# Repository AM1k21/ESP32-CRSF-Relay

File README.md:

# ESP32-CRSF-Relay

A high-performance **CRSF Relay Node** that extends the range of your radio link by forwarding CRSF packets from an ELRS Receiver to a high-power TX Module.

## 🚀 Key Capabilities

* **CRSF frames forwarding** Forwards frames from receiver to transmitter to further range of radio link
* **Dual-Core Architecture:** Radio logic runs exclusively on **Core 1** (High Priority) to ensure 0% packet loss, while WiFi runs on **Core 0**.
* **WiFi Manager:** Integrated web dashboard at `192.168.4.1` (No app required).
* **Live Telemetry:** Real-time scrolling graph of RSSI and Link Quality to visualize signal health and live channel values streaming.
* **Safety Limiter:** Adjustable throttle scaling (0-100%) via the web interface—perfect for training beginners without reprogramming the radio.
* **Smart Status:** Instantly diagnoses connection issues (e.g., "RC LOST", "MODULE OFF", "DRONE LOST").

## 🛠️ Hardware Required

* **Microcontroller:** ESP32 DevKit V1 (or compatible WROOM-32 board).
* **Input Receiver:** Any ELRS Receiver (EP1, EP2, RP1) configured to output CRSF.
* **Output Module:** A ELRS-compatible TX Module (I used **Emax Aeris Link Nano**), or an ELRS receiver flashed as TX.
* **Custom PCB:** Required to convert the ESP32's Full-Duplex UART to the Module's Half-Duplex signal. (Not needed if you are using RX as TX, since it has separate UART RX and TX pins)

# Wiring
I am using an ELRS receiver connected to a UART of ESP32, another ESPs UART is connected to a custom PCB, and from PCB to transmitter one half-duplex line, as seen on this diagram:

| Component | ESP32 Pin | Function | Notes |
| :--- | :--- | :--- | :--- |
| **Receiver TX** | GPIO 33 | Input | Connect to RX pad of ELRS Receiver |
| **Receiver RX** | GPIO 32 | Output | Connect to TX pad of ELRS Receiver |
| **Module RX** | GPIO 17 | TX Data | Connects to PCB Data Line |
| **Module TX** | GPIO 16 | RX Data | Connects to PCB Data Line |
| **Buffer EN** | GPIO 25 | Direction | Controls Half-Duplex switching |

## ⚡ Important Power Warning

**⚠️ DO NOT power high-output modules directly from the ESP32.**

If you are using high-power modules like the **Emax Aeris**, they can draw significant current (up to 2A at 1W+).
* **Low Power (10mW - 250mW):** May work on USB power, but not recommended.
* **High Power (500mW - 1000mW+):** You **MUST** use an external 2S Battery (5-21V) connected to the module's XT30 port[cite: 47, 94]. Failure to do so will cause brownouts and failsafes.

## 📱 Usage (Web Dashboard)

Once powered on, the ESP32 will broadcast a WiFi network.

1.  **Connect:** Join the WiFi network **`Comm_Relay_Manager`** (No password).
2.  **Dashboard:** Open your browser and navigate to **`http://192.168.4.1`**.
3.  **Controls:**
    * **Dashboard Tab:** View live stats, signal graphs, and channel movements.
    * **Limits Tab:** Adjust the "Max Throttle" slider to limit the output of Channel 3 for training purposes.

## 📂 PCB Design
The `PCB` folder contains KiCad project files for the **Half-Duplex Translator**.
* **Why is this needed?** ESP32 UARTs use two separate wires (TX and RX). Most RC Modules use a single shared wire for both sending commands and receiving telemetry. This PCB uses a buffer chip to merge these signals safely.

## 📚 Technical Docs (MkDocs)

A fully structured documentation site is now available in the `docs` folder and configured by `mkdocs.yml`.

### Run locally

```powershell
pip install -r requirements-docs.txt
mkdocs serve
```

Then open: `http://127.0.0.1:8000`

### Build static site

```powershell
mkdocs build
```

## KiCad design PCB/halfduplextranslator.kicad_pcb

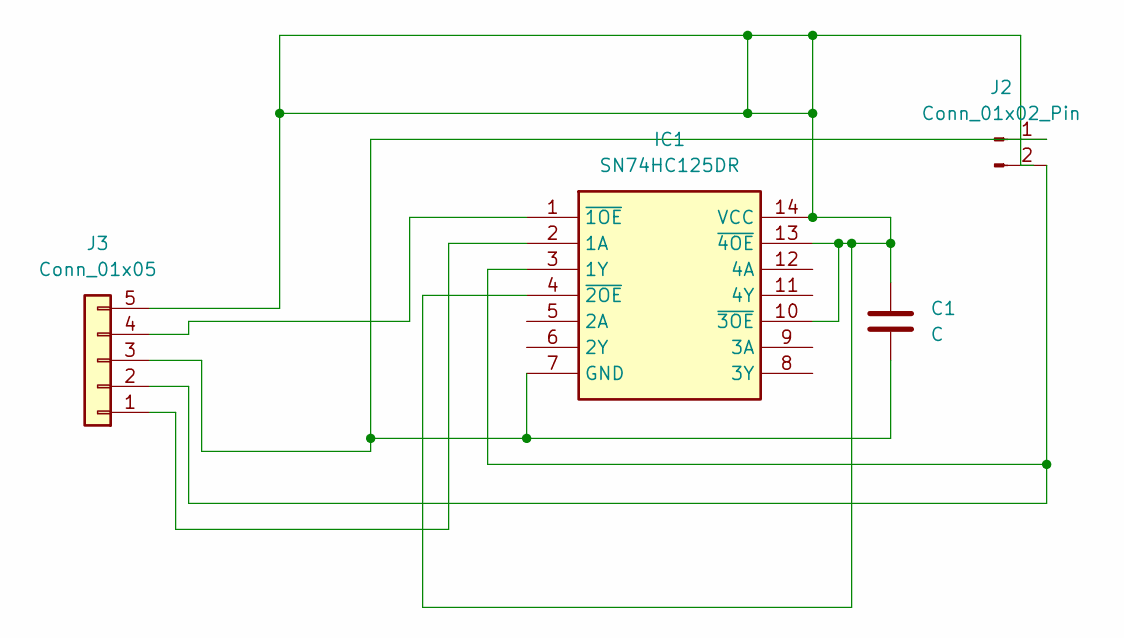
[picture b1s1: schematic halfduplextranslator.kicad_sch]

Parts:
C1: C; C_Disc_D5.0mm_W2.5mm_P5.00mm
IC1: SN74HC125DR; SOIC127P600X175-14N; Mouser Part Number 595-SN74HC125DR
J2: Conn_01x02_Pin; SolderWire-0.1sqmm_1x02_P3.6mm_D0.4mm_OD1mm_Relief
J3: Conn_01x05; SolderWire-0.1sqmm_1x05_P3.6mm_D0.4mm_OD1mm_Relief

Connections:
unnamed: IC1.2 (1A), J3.1
unnamed: IC1.3 (1Y), J2.2, J3.2
unnamed: C1.2, IC1.7 (GND), J2.1, J3.3
unnamed: C1.1, IC1.4 (~2OE), IC1.10 (~3OE), IC1.13 (~4OE), IC1.14 (VCC), J3.5
unnamed: IC1.1 (~1OE), J3.4

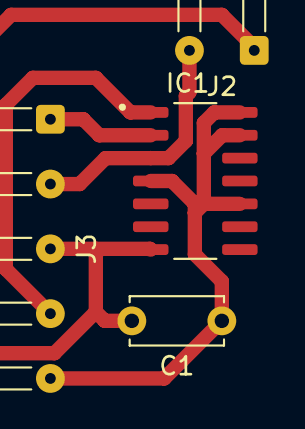
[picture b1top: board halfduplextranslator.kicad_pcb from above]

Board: 2 copper layers, 4 parts (0 on the bottom side), 5 nets.

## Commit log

2025-12-22 Added code
2025-12-22 Add KiCad ignore list to .gitignore
2025-12-22 Enhance README with project details and instructions
    Expanded project documentation with detailed capabilities, hardware requirements, wiring instructions, power warnings, usage guide, and PCB design information.
2026-03-05 docs: add comprehensive technical documentation
2026-03-05 Update technical documentation for ESP32-CRSF-Relay
2026-03-11 docs: add power supply, ELRS binding, gate usage, and latency details
2026-03-17 češki
2026-04-08 Better Wi-Fi
2026-04-08 Update print statement from 'Hello' to 'Goodbye'
2026-04-08 mkdocs upgrade

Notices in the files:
README.md:
License: MIT
